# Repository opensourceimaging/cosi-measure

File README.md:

# COSI Measure

># ⚠️ Repository Deprecated
>
>This repository is **outdated** and no longer actively maintained.
>
>All **new development, updates, and issue tracking have moved** to our new repository on GitLab:
>
>👉 **[https://gitlab.com/osii/tools/cosi-measure/](https://gitlab.com/osii/tools/cosi-measure/)**
>
>Please visit the new repository for the latest code, documentation, and contributions.
>
>Thank you for your understanding!

___

<!-- TOC -->

- [COSI Measure](#cosi-measure)
- [⚠️ Repository Deprecated](#-repository-deprecated)
    - [Description](#description)
    - [System specifications](#system-specifications)
    - [Versions and Branches](#versions-and-branches)
    - [Contacts](#contacts)
        - [Known builds](#known-builds)
    - [Contributors alphabetical order](#contributors-alphabetical-order)
    - [Publications](#publications)
    - [Acknowledgments](#acknowledgments)
    - [License and Liability](#license-and-liability)

<!-- /TOC -->
## Description

COSI Measure is an open source multipurpose 3-axis robot operating in a large volume, that can be equipped with e.g. field mapping probes for static or dynamic field measurements (electromagnetic, temperature etc.). Submillimeter fidelity and reproducibility/backlash performance were evaluated experimentally. It can be potentially upgraded to be used as a CNC, for 3D printing or other applications, that require reproducible submillimeter movements.

## System specifications 

- Dimension: (80x90x105)cm³
- Working volume: (53x53x64)cm³
- Precision: positioning error <1mm
- Max load: ~20kg
- Applied force: 896N (91kg)
- Standalone system
- Inductive limit switches
- Emergency Stop
- Open Source Software GUI (Python)
- Estimated material costs: ~2000€

More photos and videos can be found on opensourceimaging.org: https://www.opensourceimaging.org/project/cosi-measure/ 

## Versions and Branches

You're currently viewing the `main` branch, showing ongoing development on `v2.0.*` of the COSI Measure system.\
New versions are developed in dedicated feature branches and then merged here.

The latest stable release is [v2.0](https://github.com/opensourceimaging/cosi-measure/releases/tag/v2.0).

For older, please check out the [releases overview](https://github.com/opensourceimaging/cosi-measure/releases/).

The changes between versions are summarzized in the respective release notes and documented in the [CHANGELOG](CHANGELOG.md) document.

## Contacts

General contact:
Name | Email | Institution | COSI Measure Applications
-----|-----|-----|-----|
Lukas Winter | lukas.winter@ptb.de | Physikalisch-Technische Bundesanstalt (PTB), Berlin, Germany | Magnetic field mapping of MR magnets, implant safety measurements, RF field mapping of RF coils using time-domain H- and E-field sensors, Measurements within an MR scanner, 3D printing

### (Known) builds
Name | Email | Institution | COSI Measure Applications
-----|-----|-----|-----|
Haopeng Han | haopeng.han@mdc-berlin.de | Max-Delbrück Center for Molecular Medicine, Berlin, Germany | Temperature and RF field mapping of RF coils
Tom O'Reilly | t.o_reilly@lumc.nl | Leiden University Medical Center (LUMC), Leiden, Netherlands | Magnetic field mapping of low field MR magnets
Benjamin Menküc | benjamin.menkuec@fh-dortmund.de | University of Applied Sciences, Dortmund, Germany | Magnetic field mapping of low field MR magnets
Mark Bason | M.Bason@sussex.ac.uk | Quantum Systems and Devices, University of Sussex, Falmer, England | Magnetic field measurements
Wolfgang Kilian | Wolfgang.Kilian@ptb.de | Physikalisch-Technische Bundesanstalt (PTB), Berlin, Germany | 3D printing of phantoms

## Contributors (alphabetical order)
Nils Allek, Mark Bason, Jan Gregor Frintz, Haopeng Han, Amjad Kasabashy, Wolfgang Kilian, Ilia Kulikov, Benjamin Menküc, Tobias Mohr, Reiner Montag, Tom O'Reilly, David Shiers, Berk Silemek, Karl Stupic, Lukas Winter

## Publications
If you find this useful in your work, please cite:
[H. Han, R. Moritz, E. Oberacker, H. Waiczies, T. Niendorf and L. Winter, "Open Source 3D Multipurpose Measurement System with Submillimetre Fidelity and First Application in Magnetic Resonance", Scientific Reports, 7:13452, 2017](www.nature.com/articles/s41598-017-13824-z)

## Acknowledgments

This work is supported by the Open Source Imaging Initiative (OSI²), https://www.opensourceimaging.org/project/cosi-measure/

The project (21NRM05) has received funding from the European Partnership on Metrology, co-financed by the European Union's Horizon Europe Research and Innovation Programme and by the Participating States.

## License and Liability
The content in this repository is licensed under the CERN Open Hardware Licence Version 2 - Weakly Reciprocal, please see [LICENSE](LICENSE) for details and also check the [DISCLAIMER](DISCLAIMER.pdf)

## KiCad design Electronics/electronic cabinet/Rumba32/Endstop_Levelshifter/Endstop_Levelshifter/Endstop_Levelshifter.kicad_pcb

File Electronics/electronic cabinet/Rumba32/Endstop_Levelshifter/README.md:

# Endstop BreakoutBoard

This breakoutboard needs to be placed into Rumba32 Endstop connector. It is a levelshifter for the 12 V Endstops. 

12V is supplied by Rumba32, you need to connect the 12V Pins of Rumba32 to J4 of this breakout board.

## Schematic

## BOM

| ld 	| Designator 	| Quantity 	| Comment           	| Manufacturer Part No 	| Link Digikey                                                                          	|
|----	|------------	|----------	|-------------------	|----------------------	|---------------------------------------------------------------------------------------	|
| 1  	| J1         	| 1        	| Screw Terminal    	| 691210910008         	| https://www.digikey.de/de/products/detail/w%C3%BCrth-elektronik/691210910008/11478428 	|
| 2  	| C1         	| 1        	| 10n               	| C0805C103K2RECAUTO   	| https://www.digikey.de/de/products/detail/kemet/C0805C103K2RECAUTO/8646745            	|
| 3  	| J4         	| 1        	| 2 Pin Header 2.54 	| 0022289020           	| https://www.digikey.de/de/products/detail/molex/0022289020/3158803                    	|
| 4  	| J3         	| 1        	| 3 Pin Header 2.54 	| 801-87-003-10-001101	| https://www.digikey.de/de/products/detail/preci-dip/801-87-003-10-001101/3757430      	|
| 5  	| J2         	| 1        	| 5 Pin Header 2.54 	| 801-87-005-10-001101 	| https://www.digikey.de/de/products/detail/preci-dip/801-87-005-10-001101/3757433      	|
| 6  	| IC1        	| 1        	| Buffer            	| 74HC4050PW,118       	| https://www.digikey.de/de/products/detail/nexperia-usa-inc/74HC4050PW-118/1230398     	|

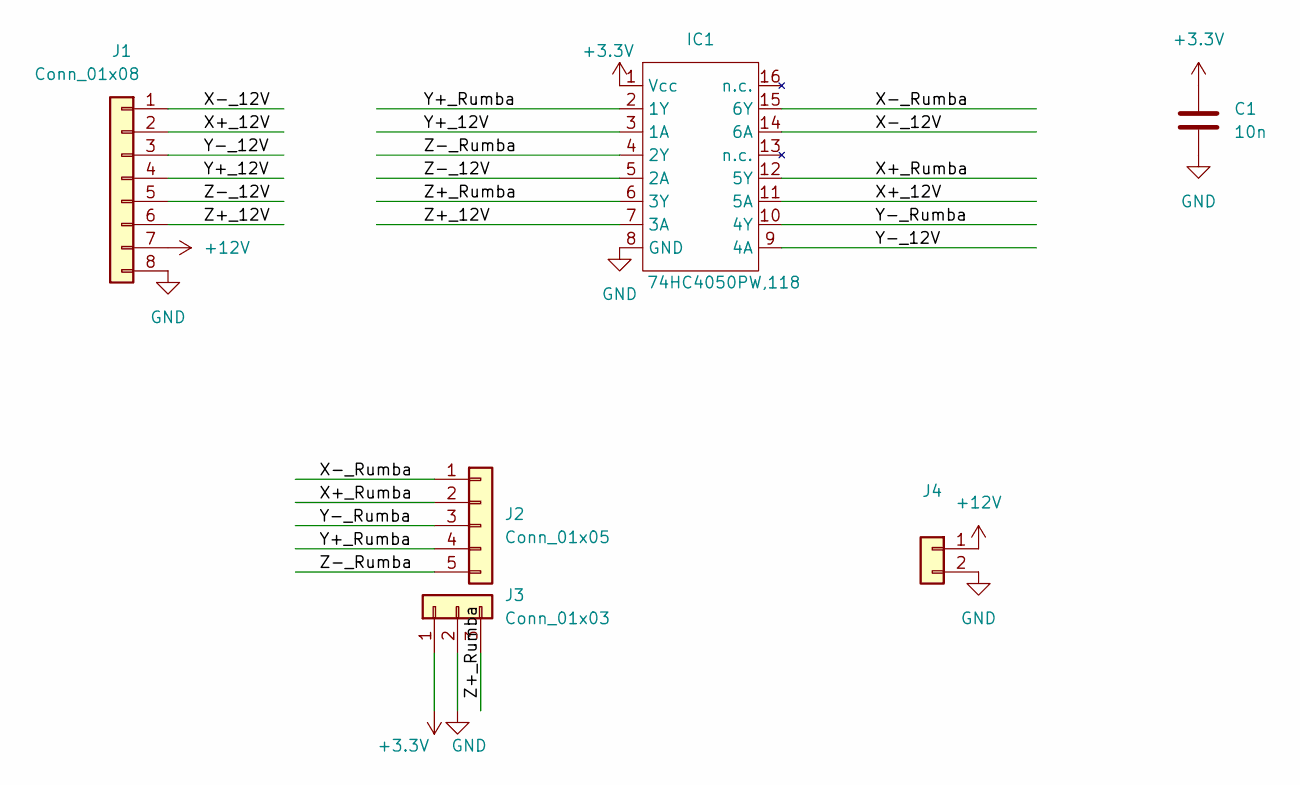
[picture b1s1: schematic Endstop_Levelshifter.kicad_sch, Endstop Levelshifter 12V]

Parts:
C1: 10n; C_0805_2012Metric_Pad1.18x1.45mm_HandSolder
IC1: 74HC4050PW,118; TSSOP-16_4.4x5mm_P0.65mm
J1: Conn_01x08; 691210910008
J2: Conn_01x05; PinSocket_1x05_P2.54mm_Vertical
J3: Conn_01x03; PinSocket_1x03_P2.54mm_Vertical
J4: Conn_01x02; PinHeader_1x02_P2.54mm_Horizontal

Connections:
+3.3V: C1.1, IC1.1 (Vcc), J3.1
+12V: J1.7, J4.1
/X+_12V: IC1.11 (5A), J1.2
/X+_Rumba: IC1.12 (5Y), J2.2
/X-_12V: IC1.14 (6A), J1.1
/X-_Rumba: IC1.15 (6Y), J2.1
/Y+_12V: IC1.3 (1A), J1.4
/Y+_Rumba: IC1.2 (1Y), J2.4
/Y-_12V: IC1.9 (4A), J1.3
/Y-_Rumba: IC1.10 (4Y), J2.3
/Z+_12V: IC1.7 (3A), J1.6
/Z+_Rumba: IC1.6 (3Y), J3.3
/Z-_12V: IC1.5 (2A), J1.5
/Z-_Rumba: IC1.4 (2Y), J2.5
GND: C1.2, IC1.8 (GND), J1.8, J3.2, J4.2

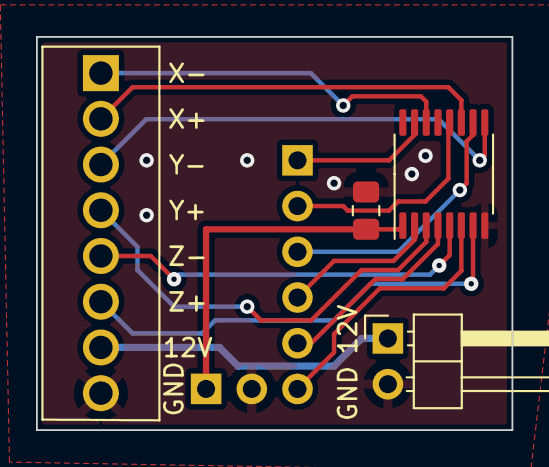
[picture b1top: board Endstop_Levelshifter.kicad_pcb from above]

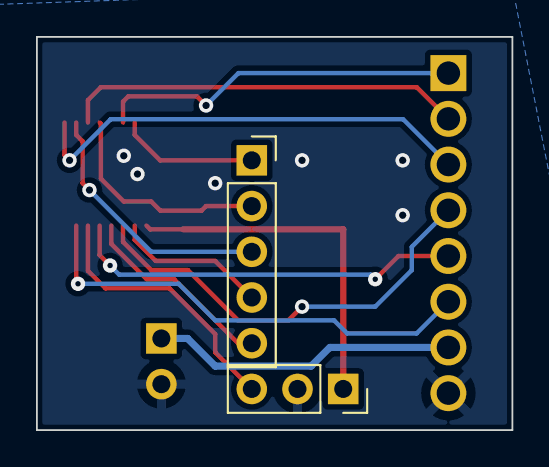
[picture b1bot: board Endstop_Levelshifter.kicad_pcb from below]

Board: 2 copper layers, 26.4 x 21.8 mm, 6 parts (2 on the bottom side), 15 nets.

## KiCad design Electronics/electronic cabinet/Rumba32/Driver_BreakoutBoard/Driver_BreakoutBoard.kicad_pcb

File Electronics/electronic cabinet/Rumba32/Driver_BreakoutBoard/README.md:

# Driver Breakout Board

<!-- TOC -->

- [Driver Breakout Board](#driver-breakout-board)
    - [Enable Logic](#enable-logic)
    - [Schematic](#schematic)
    - [BOM](#bom)
    - [Setting jumpers on Rumba32](#setting-jumpers-on-rumba32)
        - [STEPPER_DRIVER_LOGIC JUMPER](#stepper_driver_logic-jumper)
        - [Additional Software Enable Jumpers](#additional-software-enable-jumpers)

<!-- /TOC -->

This breakoutboard can be placed to the motor driver slots into the Rumba32 board. 
It is useful for wiring the step, direction and enable pins via the motor connector to external motor drivers. In addition it supports an easy way of integrating a drive-enable functionality.

## Enable Logic

There can be current on the drives, if 
- The Firmware enables the drives and
- some control pins are low (furhter explanation below) and
- Emergency Stop Relais provides it's NPN-ok signal ($0 \ V$).
- Contactor -Q1 is closed (no safe-torque-off)

Many 3D-printing firmwares are not designed for switching off the drives completly while executing a G-code file. But COSI-Measure is meant to perform magnetic measurements, so it must not disturb the measurements with noisy motor currents while performing a measurement.

A convenient workaround for Klipper is to switch on and off some extra GPIO Pins, that are wired to the hardware-enable-logic. In case you are doing something different and you do not need this feature, feel free to ignore it. Default of these Pins is low, which is also the enabled state. For details about it see the [printer.cfg](../../../software/backend/printer.cfg) file line 275-317. The drives can be enabled and disabled with g-code macros while keeping the homing active.

The NPN-ok-signal from the emergency stop relais can be daisy-chained with standard 2.54 mm jumpers to the next breakout board.

The enable input of the motordriver is not meant for a safe-torque-off function (emergency stop). Safe-torque-off is implemented in hardware (mechanical relais, contactors etc.), see [schematics](../../schematics/README.md#emergencystop). 
Anyway, to prevent driver malfunction the driver will be disabled with semiconductor only circuits before the power supply of the driver will be disconnected. The delay is coming from the slower reaction of mechanical contactors and relais, so no dedicated timing module is needed.

## Schematic

## BOM

This Bill-of-Materials is for 1 breakout board only. You need one breakout board for each motor with external motor drivers, usually 3 in total (depending to your setup).

| #  | Designator | Quantity | Comment              | Man. Part-No       | Link                                                                                            |
|----|------------|----------|----------------------|--------------------|-------------------------------------------------------------------------------------------------|
| 1  | C1         | 1        | 10 nF, 0805          | C0805C103K2RECAUTO | <https://www.digikey.de/de/products/detail/kemet/C0805C103K2RECAUTO/8646745>                    |
| 2  | D1         | 1        | Dual LED red/green   | AAA3528ESGCT       | <https://www.digikey.de/de/products/detail/kingbright/AAA3528ESGCT/7318936>                     |
| 3  | IC1        | 1        | OR-Gate              | SN74ACT32PWR       | <https://www.digikey.de/en/products/detail/texas-instruments/SN74ACT32PWR/376063>               |
| 4  | J1, J2     | 2        | 8 pin header 2.54    | 61300811121        | <https://www.digikey.de/de/products/detail/w%C3%BCrth-elektronik/61300811121/4846839>           |
| 5  | J3, J5     | 2        | 2 pin header 2.54    | 61300211121        | <https://www.digikey.de/de/products/detail/w%C3%BCrth-elektronik/61300211121/4846823>           |
| 6  | J4         | 1        | 2 pos screw terminal | 0393570002         | <https://www.digikey.de/de/products/detail/molex/0393570002/946543>                             |
| 7  | Q1         | 1        | NPN Transistor       | MMBT3904           | <https://www.digikey.de/de/products/detail/micro-commercial-co/MMBT3904-TP/717280>              |
| 8  | R1         | 1        | 47 kOhm, 0805        | WR08X473 JTL       | <https://www.digikey.de/de/products/detail/walsin-technology-corporation/WR08X473-JTL/13240617> |
| 9  | R2         | 1        | 270 Ohm, 0805        | RMCF0805JT270R     | <https://www.digikey.de/de/products/detail/stackpole-electronics-inc/RMCF0805JT270R/1757887>    |
| 10  | R3, R5    | 2        | 200 Ohm, 0805        | RMCF0805FT200R     | <https://www.digikey.de/de/products/detail/stackpole-electronics-inc/RMCF0805FT200R/1760343>    |
| 11 | R4         | 1        | 1.2 kOhm, 0805       | RMCF0805JT1K20     | <https://www.digikey.de/de/products/detail/stackpole-electronics-inc/RMCF0805JT1K20/1757811>    |
| 12 | -          | 3        | 2.54 mm jumper       | QPC02SXGN-RC       | <https://www.digikey.de/en/products/detail/sullins-connector-solutions/QPC02SXGN-RC/2618262>    |

## Setting jumpers on Rumba32

### STEPPER_DRIVER_LOGIC JUMPER 

The STEPPER_DRIVER_LOGIC jumper (see picture below) selects the logic voltage supplied to all stepper driver
sockets. By default, it is configured so that 3.3V is supplied to the stepper drivers. However, since the external motor drivers need 5 V, the track between the centre and 3V pad should be cut, and a solder joint placed over the 5V and centre pad. <br>
 <br>
(picture and parts of the text above borrowed from https://github.com/Aus3D/RUMBA32/blob/master/Resources/Manual/RUMBA32%20V1.1%20User%20Manual%20-%20REV%20A.pdf, License: GPLv2)

### Additional Software Enable Jumpers
Set the jumpers beneath the breakoutboards as seen in the picture below (blue):

 <br>
(Picture borrowed and modified from https://github.com/Aus3D/RUMBA32?tab=readme-ov-file, License: GPLv2)

These jumpers are connecting some GPIO-Pins to the enable logic of this breakout board.

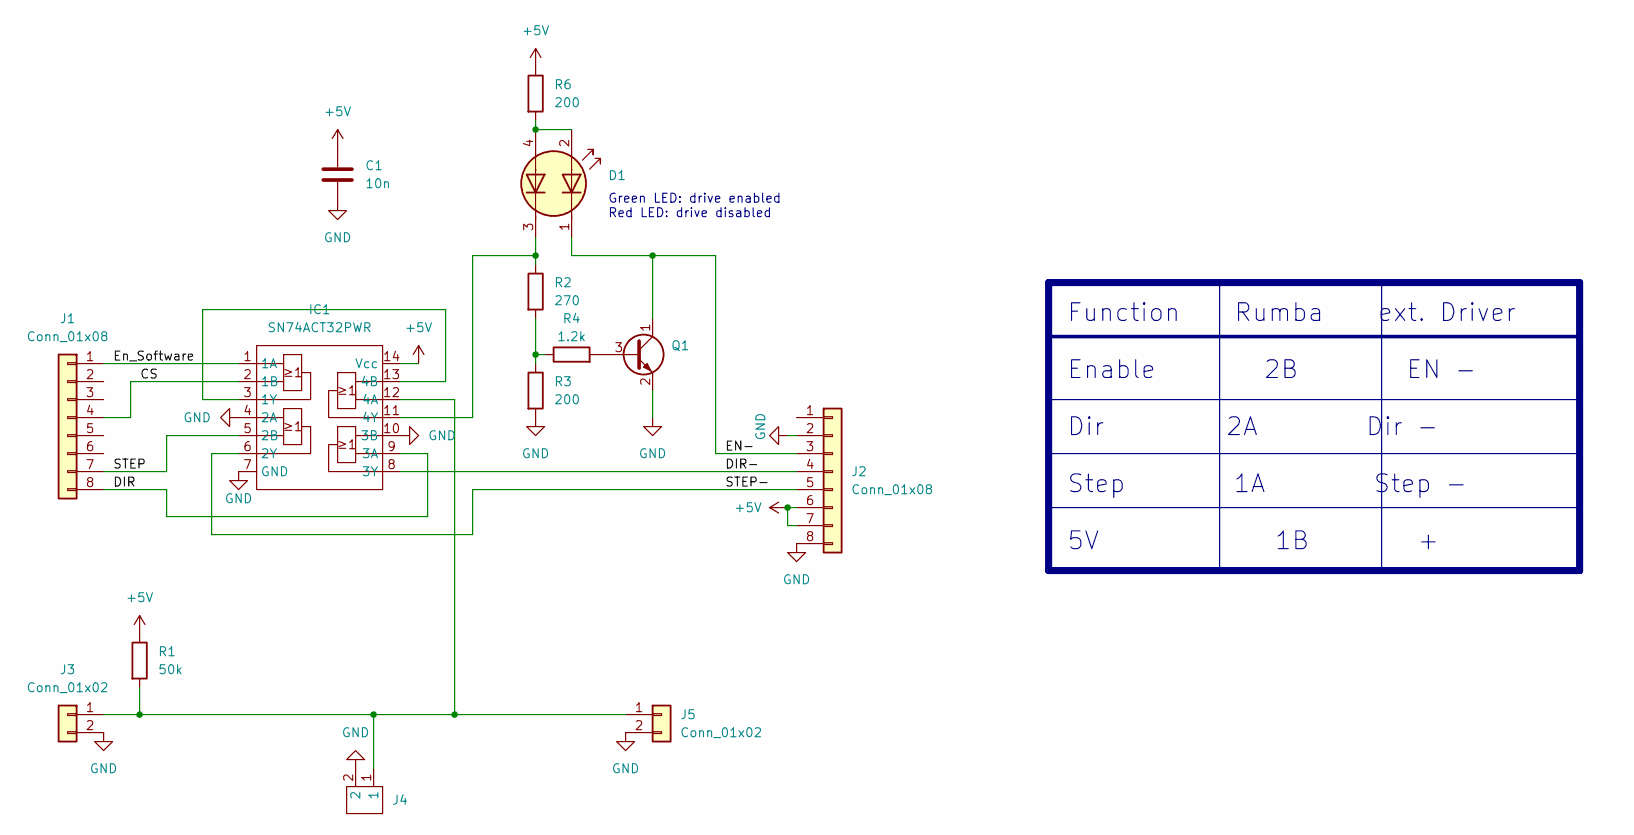
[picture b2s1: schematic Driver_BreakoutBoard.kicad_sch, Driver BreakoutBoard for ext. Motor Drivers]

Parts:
C1: 10n; C_0805_2012Metric_Pad1.18x1.45mm_HandSolder
D1: LED_Dual; LED_Kingbright_AAA3528ESGCT
IC1: SN74ACT32PWR; SOT402-1_NXP-M
J1, J2: Conn_01x08; PinHeader_1x08_P2.54mm_Vertical
J3, J5: Conn_01x02; PinHeader_1x02_P2.54mm_Vertical
J4: 0393570002
Q1: Q_NPN_CEB; SOT-23_Handsoldering
R1: 50k; R_0805_2012Metric_Pad1.20x1.40mm_HandSolder
R2: 270; R_0805_2012Metric_Pad1.20x1.40mm_HandSolder
R3, R6: 200; R_0805_2012Metric_Pad1.20x1.40mm_HandSolder
R4: 1.2k; R_0805_2012Metric_Pad1.20x1.40mm_HandSolder

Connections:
+5V: C1.1, IC1.14 (Vcc), J2.6, J2.7, R1.1, R6.1
/CS: IC1.2 (1B), J1.4
/DIR: IC1.9 (3A), J1.8
/DIR-: IC1.8 (3Y), J2.4
/EN-: D1.1 (A1), J2.3, Q1.1 (C)
/En_Software: IC1.1 (1A), J1.1
/STEP: IC1.5 (2B), J1.7
/STEP-: IC1.6 (2Y), J2.5
GND: C1.2, IC1.4 (2A), IC1.7 (GND), IC1.10 (3B), J2.2, J2.8, J3.2, J4.2, J5.2, Q1.2 (E), R3.2
unnamed: D1.3 (A2), IC1.11 (4Y), R2.1
unnamed: IC1.3 (1Y), IC1.13 (4B)
unnamed: IC1.12 (4A), J3.1, J4.1, J5.1, R1.2
unnamed: Q1.3 (B), R4.2
unnamed: R2.2, R3.1, R4.1
unnamed: D1.2 (K1), D1.4 (K2), R6.2

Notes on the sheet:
Function Rumba ext. Driver Enable 2B EN - Dir 2A Dir - Step 1A Step - 5V 1B +
Green LED: drive enabled Red LED: drive disabled

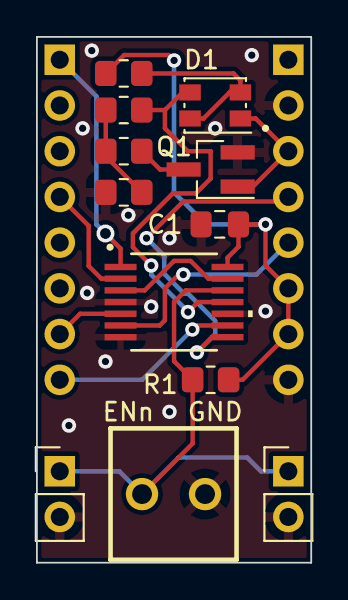
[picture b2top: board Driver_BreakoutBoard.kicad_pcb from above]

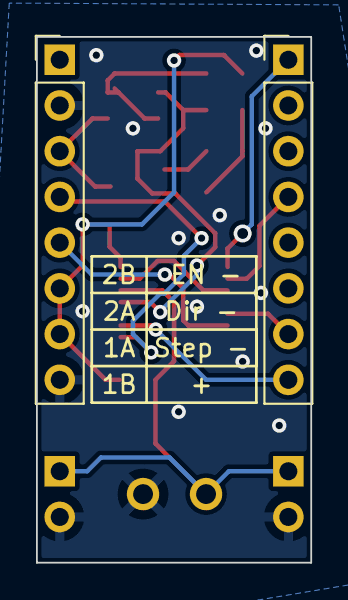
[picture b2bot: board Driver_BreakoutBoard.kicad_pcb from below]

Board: 2 copper layers, 15.2 x 29.2 mm, 14 parts (2 on the bottom side), 15 nets.

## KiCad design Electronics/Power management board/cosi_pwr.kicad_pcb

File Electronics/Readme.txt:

Here you can find all necessary files to reproduce the COSI Measure electrical assembly.

Please read the assembly documentation first, in particular you will find some known issues or useful ideas in the comments section, which will help you reproducing the design.

Folder: Figures
Additional high resolution figures that might help with understanding the functionality of the design.

Folder: J5-Bob
PCB files of the J5-Bob that is needed with the BeBoPr++.

Folder: Manuals, Datasheets, etc
Relevant manuals, datasheets of the project.

Folder: Power management board
PCB files and code for the power management board.

File: *_BoM_electronics.ods and *_BoM_electronics.pdf
Bill of materials for the electronical components and the casing. The .ods file can be opened with LibreOffice Cald (https://www.libreoffice.org/, the open source counterpart to Excel). 

Files: *_casing_assembly_instructions.odt and *_casing_assembly_instructions.pdf
Electrical step by step assembly documentation. The .odt file can be opened with LibreOffice Writer (https://www.libreoffice.org/, the open source counterpart to Word).

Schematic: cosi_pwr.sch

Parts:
C1, C5: 100u; CPOL-RADIAL-100UF-25V
C2, C6: 4.7u; C_0805_HandSoldering
C3, C7: 0.1u; C_0805_HandSoldering
D1, D2: 1N4004; DO41-10
IO1, IO2: 1X20
JP1: 2X02
JP2, JP3: 1X06
K1: PT371512; PT-3
K2: G5SB
L1: MESC-120M-01
R1, R5, R9: 1k; R0603
R2, R6, R7, R8, R11, R12, R13, R14, R15, R16, R17, R18, R19, R20, R21, R22: 10k; R0603
R10: 1k; R_0805_HandSoldering
U1: IRM_15_20
U2: DCDC_SIM1_DIP8
U3, U5, U6, U7, U8, U9, U10, U11: N-CHANNEL-MOSFET-BSS138; SOT-23_Handsoldering
X1, X2, X3: AK500_3
X4, X5, X6: AK500_2

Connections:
+3V3: IO2.19, R9.2, R10.2
+5V: C6.1, C7.1, IO1.19, R7.2, R11.2, R13.2, R15.2, R17.2, R19.2, U2.5, U6.1, U7.1, U8.1, U9.1, U10.1, U11.1
+12V: C1.1, C2.1, C3.1, C5.1, D2.C, K2.1, K2.2, L1.P$1, U1.V+
/+1.8V: IO2.18
/AC_L: K1.31, U1.AC/L, X1.1
/AC_N: K1.11, U1.AC/N, X1.3
/BANK1_0: IO2.1
/BANK1_1: IO2.2
/BANK1_2: IO2.3
/BANK1_3: IO2.4
/BANK1_4: IO2.5, JP1.4, R21.2
/BANK1_5: IO2.6
/BANK1_6: IO2.7
/BANK1_7: IO2.8
/BANK1_8: IO2.9
/BANK1_9: IO2.10, JP1.2, R22.2
/BANK1_10: IO2.11
/BANK1_11: IO2.12
/BANK1_12: IO2.13
/BANK1_13: IO2.14
/BANK1_14: IO2.15
/BANK1_15: IO2.16, R5.1
/BANK1_VCC: IO2.17
/BANK2_0: IO1.1
/BANK2_1: IO1.2
/BANK2_2: IO1.3
/BANK2_3: IO1.4
/BANK2_4: IO1.5
/BANK2_5: IO1.6
/BANK2_6: IO1.7
/BANK2_7: IO1.8
/BANK2_8: IO1.9
/BANK2_9: IO1.10
/BANK2_10: IO1.11
/BANK2_11: IO1.12
/BANK2_12: IO1.13
/BANK2_13: IO1.14
/BANK2_14: IO1.15
/BANK2_15: IO1.16, R1.1
/BANK2_16: IO1.17
/BANK2_VCC: IO1.18
/N$1: R1.2, R2.2, U3.1
/N$2: D1.A, K1.A2 (2), U3.3
/N$4: L1.P$2, U2.4
/N$14: R5.2, R6.2, U5.1
/N$15: D2.A, K2.5, U5.3
/N$19: JP1.1, R9.1
/N$20: JP1.3, R10.1
/SW_X+_H: JP3.1, R12.1, U7.3
/SW_X+_L: JP2.1, R11.1, U7.2
/SW_X-_H: JP3.2, R14.1, U8.3
/SW_X-_L: JP2.2, R13.1, U8.2
/SW_Y+_H: JP3.3, R8.1, U6.3
/SW_Y+_L: JP2.3, R7.1, U6.2
/SW_Y-_H: JP3.4, R16.1, U9.3
/SW_Y-_L: JP2.4, R15.1, U9.2
/SW_Z+_H: JP3.5, R18.1, U10.3
/SW_Z+_L: JP2.5, R17.1, U10.2
/SW_Z-_H: JP3.6, R20.1, U11.3
/SW_Z-_L: JP2.6, R19.1, U11.2
GND: C1.2, C2.2, C3.2, C5.2, C6.2, C7.2, IO1.20, IO2.20, R2.1, R6.1, R21.1, R22.1, U1.V-, U2.1, U2.7, U3.2, U5.2, X4.2, X5.2, X6.2
unnamed: K1.14 (S), X2.3, X3.3
unnamed: K1.34 (S), X2.1, X3.1
PE: X1.2, X2.2, X3.2
VCC_+12V: D1.C, K1.A1 (1), K2.3, R8.2, R12.2, R14.2, R16.2, R18.2, R20.2, X4.1, X5.1, X6.1

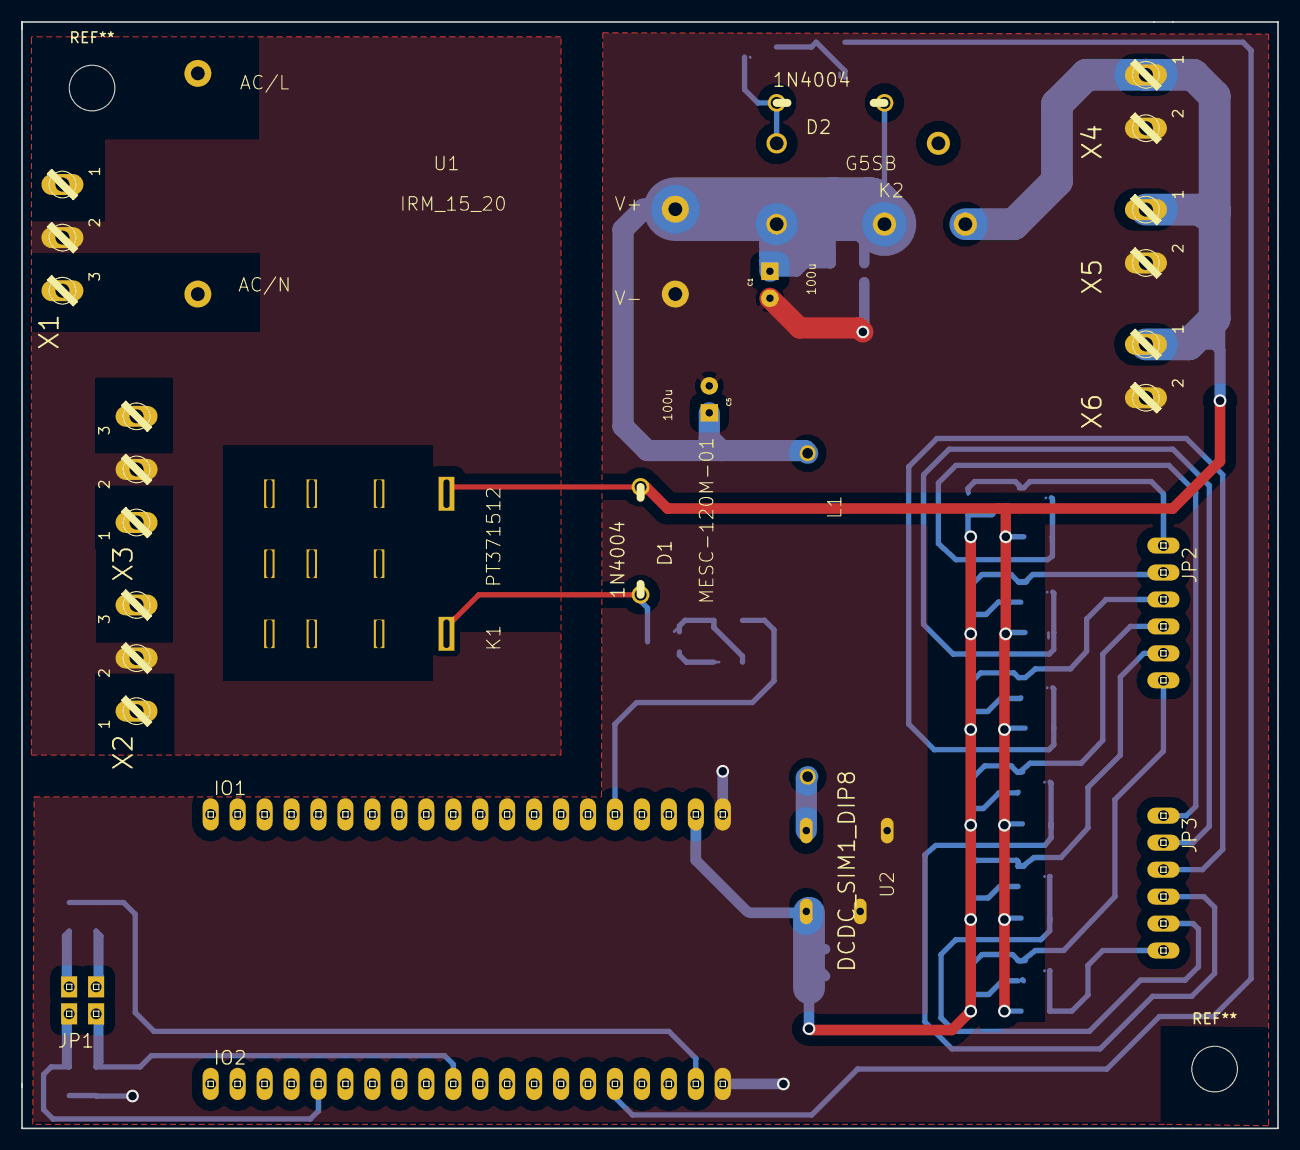
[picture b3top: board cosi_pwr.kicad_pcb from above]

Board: 2 copper layers, 118.4 x 104.3 mm, 52 parts (0 on the bottom side), 33 nets.

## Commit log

2017-10-10 Initial commit v1.0
2017-10-10 clean up
2017-10-11 Updated BOM and partlist
2017-10-13 publication link added
2018-08-09 Aluplates design files in FreeCAD v0.17
2018-08-09 Technical drawings of Aluplates designed with FreeCAD v0.17
2018-08-13 Missing dimension added to Aluplate 8
2018-08-13 Missing dimension added to tech drawing
2018-08-13 Missing dimensions added to tech drawing
2018-08-13 Missing dimensions added
2018-08-15 updated tech drawings
2018-08-15 tech drawing updated
2018-08-15 updated tech drawing
2018-08-28 Updated mechanical documentation and CAD files of the Aluplates.
2018-08-28 Updated mechanical assembly documentation
2018-08-28 Updated BoM files
2018-08-28 naming error corrected
2018-08-30 small changes in documentation
2018-09-03 small correction plate 4 and corresponding documentation/BoM
2018-10-09 Updated BoM electronics file
2018-10-11 Changed hole distance of plate 9
2018-10-11 updated BoM, pin strip mates and cable chain
2018-11-12 Casing files uploaded and BoM updated
2019-01-11 Casing assembly documentation, electrical assembly documentation added, compiled CPLD code added and a bit of reordering.
2019-01-25 Updated KiCAD + Gerber files of the power managment board.
2019-03-04 documentation update on the J5-Bob
2019-04-25 Updated Limitswitchholder files (FreeCAD).
2019-06-19 - software instructions added
2020-07-07 limit and cable chain holder v2
    More robust limit switch holder and cable chain holder version
2020-07-07 casing alternative
    (Classical) casing alternative
2021-01-05 minor additions
2021-01-05 photo added
2021-08-09 limit switch holder alternatives
    Alternative CAD files for the limit switch holders for the x- and z-axis
2021-08-09 probe holder CAD files
    CAD files for various probes
2021-10-14 Pathfile scripts
    Scripts to create pathfiles for COSI Measure added: snail, sphere, spiral
2024-04-05 cosi2 gui with qt5
2024-04-08 plotter, import paths, fake comm, following path
2024-04-08 following path works on cosi2
2024-04-09 magnet position plotted, btns for smooth moves
2024-04-09 gaussmeter hooked
2024-04-09 magnet plotted
2024-04-09 merging
2024-04-09 fake gaussmeter
2024-04-09 from COSI2
2024-04-10 field measured along path on cosi
2024-04-10 steps, position queries, magnetometer reads
2024-04-10 fields for mag pos, quick home btns
2024-04-11 gaussmeter on cosi2
2024-04-11 cosi2 before Jan
2024-04-11 movements to the magnet on cosi2
2024-04-11 command edit to cosi
2024-04-12 path generator
2024-04-12 measurement taken
2024-04-16 magnet installed on main platform
2024-04-16 magnet is turned backwards no path files
2024-04-16 sphere is a cube
2024-04-17 overnight wrong points
2024-04-17 magnet coords logged
2024-04-17 data taken without magnet
2024-04-17 description of experiment on 240416
2024-04-17 ball path snaked
2024-04-18 overnight data taken ball 100
2024-04-18 b0 scan taken ball 100
2024-04-18 tight layout and full snake in ball path
2024-04-18 100 mm scan with averages in mT
2024-04-19 overnight B0 measurements, coarse balls
2024-04-29 field viewer module
2024-04-29 240429 B0 data recorded
2024-05-02 b0 viewer euler rotations
2024-05-03 viewer gui updated
2024-05-03 export path in magnet coordinates, centered
2024-05-03 weird plotting in field viewer
2024-05-06 field viewer in 3 projections
2024-05-07 csv export in field viewer
2024-05-08 b0 exported in mag coordinates, writing only b0z
2024-05-13 2d field viewer added. mess with flipped coordinates in meshgrid
2024-05-15 multithreading
2024-05-16 csv import/export in field viewer module
2024-05-17 adding new electronics
2024-05-17 del unneeded stuff
2024-05-17 removing old limit switches
2024-05-17 adding notes about cable selection + sensor-actuator bixes
2024-05-17 adding docs for new endstops
2024-05-17 converted another README to markdown
2024-05-17 removing old software
2024-05-17 adding firmware + software backend
2024-05-17 updating license
2024-05-17 adding software from https://github.com/rst030/cosi-measure/tree/master/Software/COSI2
2024-05-17 adding limit switch holders by Tobias Mohr
2024-05-17 changed to machine readable license
2024-05-17 fixing README
2024-05-17 csv import/export, synthetic data, coords fixed in 2d plots
2024-05-21 shim rings plotted at x=0
2024-05-22 ready for B0 scan
2024-05-23 b0 data no additional magnet
2024-05-23 b0 scan with magnet on a side
2024-05-23 cross paths for gradients
2024-05-23 gradients data no amp
2024-05-24 gradient mapping
2024-05-24 1d data for gradients
2024-05-24 slow scan done
2024-05-27 weekend data
2024-05-27 weekend data no colons
2024-05-29 Update CONTRIB.TXT -> Updated email address
2024-06-03 open changelog
2024-06-30 Update bom-electronic-cabinet.csv
    Changed enclosure type to NSYS3D6420P.
2024-09-21 rewrote software. no GUI yet
2024-09-23 adding spherical harmonic decomposition, + code sugar
2024-09-24 adding reliability to serial communication + code sugar
2024-09-24 adding magnet types to coord transformations
2024-09-24 adding cosi 2 magnet V2.1 transformation
2024-09-25 optimized interface to csv importer
2024-09-25 remove unneeded file
2024-10-24 Master (#11)
    * rewrote software. no GUI yet
    * adding spherical harmonic decomposition, + code sugar
    * adding reliability to serial communication + code sugar
    * adding magnet types to coord transformations
    * adding cosi 2 magnet V2.1 transformation
    * optimized interface to csv importer
